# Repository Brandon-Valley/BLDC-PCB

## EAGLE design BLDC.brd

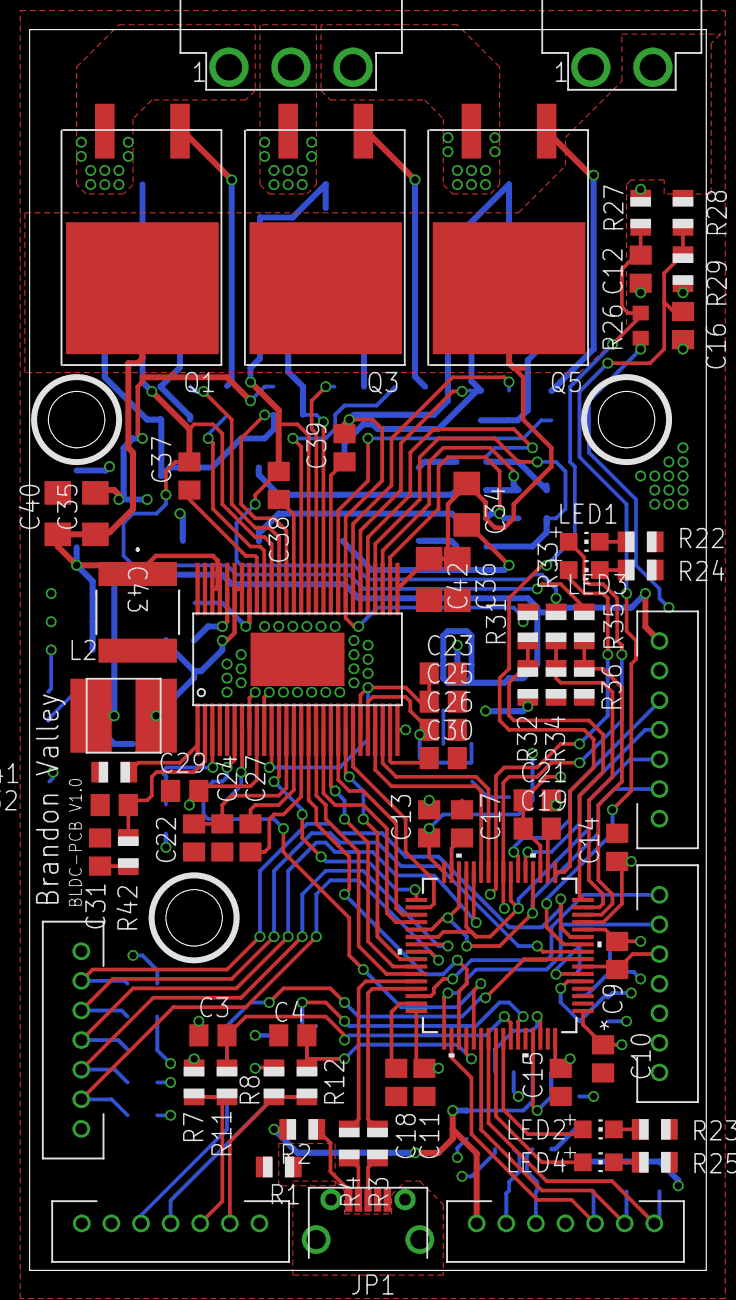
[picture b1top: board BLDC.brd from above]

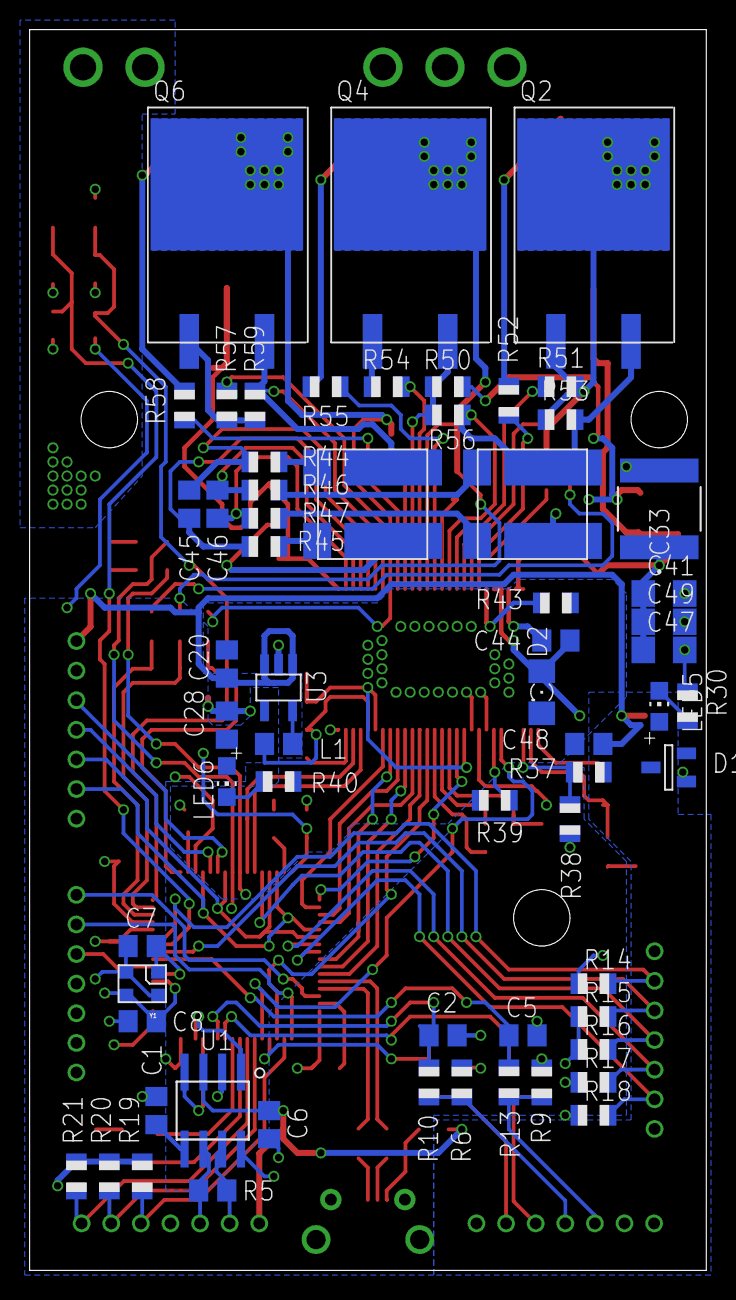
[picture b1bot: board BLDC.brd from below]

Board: 2 copper layers, 45.7 x 83.8 mm, 137 parts (62 on the bottom side), 110 nets.

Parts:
C1, C6: 0.1uF; C0805
C2, C3, C4, C5: 4n7; C0805
C7, C8: 15p; C0805
C9, C16, C44: 100n; C0805
C10, C11, C12, C13, C14, C15, C17, C18, C19, C21, C22, C23, C24, C25, C26, C29, C30: 2.2uf; C0805
C20: 4.7uF; C0805
C27: 22n; C0805
C28: 10uF; C0805
C31: 6.8n; C0805
C32: 120pf; C0805
C33, C43: 15uf,100V; K-55
C34, C35, C36, C40, C41, C42, C47, C49: 10uf,50V; C1206
C37, C38, C39: 220n; C0805
C45, C46: 2.2n; C0805
C48: 100uf; C0805
D1: 5V; SOT-23_DIODE
D2: 1206-DIODE
J1, J2, J3, J4, J5: JST-1X7
J6: IPBT-103-H1-XX-S-RA
J7: IPBT-102-H1-XX-S-RA
JP1: MOLEX-MICROUSB-B-105017-0001
L1: 2.2uH; 0805
L2: 22uH; TYS5040220M-10
LED1, LED2, LED5, LED6: GREEN; CHIP-LED0805
LED3, LED4: RED; CHIP-LED0805
Q1, Q2, Q3, Q4, Q5, Q6: D2PAK
R1, R13, R50: 0k; R0805
R2: DNP; R0805
R3, R4: 22R; R0805
R5: 120R; R0805
R6, R7, R8, R29, R32, R34, R36: 2.2k; R0805
R9, R10, R11, R12, R39: 10k; R0805
R14, R15, R16, R17, R18, R19, R20, R21, R22, R23, R24, R25, R30, R40: 1k; R0805
R26: 10K; 0603
R27: 10K; R0805
R28: 39K; R0805
R31, R33, R35, R53, R56, R59: 39k; R0805
R37: 18K; R0805
R38: 3K3; R0805
R41: 220K; R0805
R42: 15K; R0805
R43: 1M; R0805
R44, R45, R46, R47: 100R; R0805
R48, R49: .001R; 2726
R51, R52, R54, R55, R57, R58: 4.7R; R0805
U1: MCP2562; SOIC8-N_MC
U2: STM32F405RGT6; LQFP-64
U3: LM3671MF-3.3/NOPB; SOT23-5
U4: DRV8302; HTSSOP-56
Y1: 8MHz; 4-SMD

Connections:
+3V3: C1.1, C10.1, C11.1, C13.1, C14.1, C15.1, C19.1, C21.1, C26.1, C28.1, C29.1, J1.P$2, J2.P$6, L1.2, LED6.A, R6.2, R7.2, R8.2, R9.2, R26.2, U1.5, U2.1, U2.13, U2.19, U2.32, U2.48, U2.64, U3.4, U4.9, U4.24
+5V: C6.1, C20.1, C48.1, D1.K, J1.P$1, J3.P$7, J4.P$6, J5.P$7, L2.P$2, LED5.A, R2.2, R37.1, U1.3, U3.1, U3.3
ADC_TEMP: C12.1, R26.1, R27.2, U2.17
AN_IN: C16.1, R28.2, R29.1, U2.10
AUX_1: J5.P$6, R14.2, U2.11
AUX_2: J5.P$5, R15.2, U2.9
AUX_3: J5.P$4, R16.2, U2.28
AUX_4: J5.P$3, R17.2, U2.39
AUX_5: J5.P$2, R18.2, U2.40
AUX_6: J3.P$3, R19.2, U2.50
AUX_7: J3.P$2, R20.2, U2.54
AUX_8: J3.P$1, R21.2, U2.55
BR_SO1: U2.27, U4.25
BR_SO2: U2.26, U4.26
CAR_CAN_N: J3.P$5, R5.1, U1.6
CAR_CAN_P: J3.P$6, R5.2, U1.7
CAR_CAN_RX: U1.4, U2.61
CAR_CAN_TX: U1.1, U2.62
DC_CAL: U2.33, U4.12
EN_GATE: U2.51, U4.16
FAULT: U2.53, U4.6
GND: C1.2, C2.2, C3.2, C4.2, C5.2, C6.2, C7.1, C8.1, C9.2, C10.2, C11.2, C12.2, C13.2, C14.2, C15.2, C16.2, C17.2, C18.2, C19.2, C20.2, C21.2, C22.2, C23.2, C24.2, C25.2, C26.2, C28.2, C29.2, C30.2, C31.2, C32.2, C33.2, C34.2, C35.2, C36.2, C40.2, C41.2, C42.2, C43.2, C47.2, C48.2, C49.2, D1.A, D2.A, J1.P$7, J2.P$7, J3.P$4, J4.P$1, J5.P$1, J7.1, JP1.5, JP1.P$5, R1.1, R14.1, R15.1, R16.1, R17.1, R18.1, R19.1, R20.1, R21.1, R22.1, R23.1, R24.1, R25.1, R27.1, R29.2, R30.1, R32.1, R34.1, R36.1, R38.2, R39.1, R40.1, R41.2, R43.2, R48.BL, R49.BL, R50.1, U1.2, U1.8, U2.12, U2.18, U2.60, U2.63, U3.2, U4.8, U4.10, U4.28, U4.57, Y1.2, Y1.4
H1: U2.43, U4.17
H1_LOW: Q2.A2, R49.BR, R53.2, R56.1, U4.44
H1_VS: C37.2, J6.1, Q1.A2, Q2.K, R35.1, U4.46
H2: U2.42, U4.19
H2_LOW: Q4.A2, R50.2, R56.2, U4.39
H2_VS: C38.2, J6.2, Q3.A2, Q4.K, R33.1, U4.41
H3: U2.41, U4.21
H3_LOW: Q6.A2, R48.BR, R59.2, U4.34
H3_VS: C39.2, J6.3, Q5.A2, Q6.K, R31.1, U4.36
HALL_1_IN: J4.P$4, R6.1, R10.1
HALL_1_OUT: C2.1, R10.2, U2.59
HALL_2_IN: J4.P$3, R7.1, R11.1
HALL_2_OUT: C3.1, R11.2, U2.58
HALL_3_IN: J4.P$2, R8.1, R12.1
HALL_3_OUT: C4.1, R12.2, U2.52
L1: U2.36, U4.18
L2: U2.35, U4.20
L3: U2.34, U4.22
LED_GREEN_1: LED1.A, U2.24
LED_GREEN_2: LED2.A, U2.57
LED_RED_1: LED3.A, U2.25
LED_RED_2: LED4.A, U2.56
MISO_ADC_EXT2: J1.P$3, U2.22
M_H1: R52.1, U4.47
M_H2: R55.1, U4.42
M_H3: R58.1, U4.37
M_L1: R51.1, U4.45
M_L2: R54.1, U4.40
M_L3: R57.1, U4.35
unnamed: LED3.C, R24.2
unnamed: LED2.C, R23.2
unnamed: JP1.2, JP1.P$2, R4.2
unnamed: JP1.3, JP1.P$3, R3.2
unnamed: JP1.1, JP1.P$1, R2.1
unnamed: C18.1, U2.47
unnamed: C8.2, U2.5, Y1.3
unnamed: C7.2, U2.6, Y1.1
unnamed: R41.1, U4.1
unnamed: C31.1, R42.1
unnamed: L1.1, U3.5
unnamed: C32.1, R42.2, U4.2
unnamed: R37.2, R38.1, U4.3
unnamed: R39.2, U4.7
unnamed: C23.1, C25.1, U4.11, U4.23
unnamed: C22.1, C24.1, U4.13
unnamed: C27.1, U4.14
unnamed: C30.1, U4.27
unnamed: C27.2, U4.15
unnamed: C44.1, U4.52
unnamed: C44.2, D2.C, L2.P$1, U4.50, U4.51
unnamed: R43.1, U4.49
unnamed: C37.1, U4.48
unnamed: C45.1, R44.1, U4.33
unnamed: C38.1, U4.43
unnamed: C45.2, R45.1, U4.32
unnamed: C39.1, U4.38
unnamed: C46.2, R47.1, U4.30
unnamed: C46.1, R46.1, U4.31
unnamed: Q1.A1, R52.2
unnamed: Q3.A1, R55.2
unnamed: Q5.A1, R58.2
unnamed: Q2.A1, R51.2, R53.1
unnamed: Q4.A1, R54.2
unnamed: Q6.A1, R57.2, R59.1
unnamed: C17.1, U2.31
unnamed: LED1.C, R22.2
unnamed: LED4.C, R25.2
unnamed: LED5.C, R30.2
unnamed: LED6.C, R40.2
NRST: C9.1, J2.P$3, U2.7
RX_SCL_MOSI: J1.P$5, U2.23, U2.29, U2.38
SCK_ADC_EXT: J1.P$4, U2.21
SENS1: R31.2, R32.2, U2.16
SENS2: R33.2, R34.2, U2.15
SENS3: R35.2, R36.2, U2.14
SGND: JP1.P$6, JP1.P$7, JP1.P$8, JP1.P$9, R1.2
SH1_A: R44.2, R48.TR
SH1_B: R45.2, R48.TL
SH2_A: R46.2, R49.TR
SH2_B: R47.2, R49.TL
SWCLK: J2.P$2, U2.49
SWDIO: J2.P$1, U2.46
TEMP_IN: J4.P$5, R9.1, R13.2
TEMP_MOTOR: C5.1, R13.1, U2.8
TX_SDA_NSS: J1.P$6, U2.20, U2.30, U2.37
USB_DM: R4.1, U2.44
USB_DP: R3.1, U2.45
VCC: C33.1, C34.1, C35.1, C36.1, C40.1, C41.1, C42.1, C43.1, C47.1, C49.1, J7.2, Q1.K, Q3.K, Q5.K, R28.1, U4.29, U4.53, U4.54

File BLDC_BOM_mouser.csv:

Qty-1,Part References,Value,Package,Mfg Part Num,Mfg Name,VID,Vendor Part Num,Description,Pkg Code,,,,,,XREF
1,"J7",,IPBT-102-H1-XX-S-RA,***PART# '*' NOT FOUND***,*,*,*,*,*,*,*,*,*,*,*
1,"J6",,IPBT-103-H1-XX-S-RA,***PART# '*' NOT FOUND***,*,*,*,*,*,*,*,*,*,*,*
5,"J1, J2, J3, J4, J5",,JST-1X7,***PART# '*' NOT FOUND***,*,*,*,*,*,*,*,*,*,*,*
1,"JP1",,MOLEX-MICROUSB-B-105017-0001,***PART# '*' NOT FOUND***,*,*,*,*,*,*,*,*,*,*,*
1,"D2",,1206-DIODE,CD1206-B260,Bourns Inc.,DK,CD1206-B260CT-ND,Diode Schottky 60V 2A Surface Mount 1206,Chip, Concave Terminals,*,*,*,*,*,*
6,"Q1, Q2, Q3, Q4, Q5, Q6",,D2PAK,IRFS7530TRLPBF,Infineon Technologies,DK,IRFS7530TRLPBFCT-ND,N-Channel 60V 195A (Tc) 375W (Tc) Surface Mount D²PAK (TO-263AB),TO-263-7, D²Pak (6 Leads + Tab),*,*,*,*,*,*
2,"R48, R49",.001R,2726,***PART# '*' NOT FOUND***,*,*,*,*,*,*,*,*,*,*,*
2,"C1, C6",0.1uF,C0805,GRM21BR71E104KA01L,Murata Electronics North America,DK,490-1673-1-ND,CAP CER 0.1UF 25V 10% X7R 0805,0805 (2012 Metric),*,*,*,*,*,REF43
3,"R1, R13, R50",0k,R0805,ERJ-6GEY0R00V,Panasonic Electronic Components,DK,P0.0ACT-ND,RES SMD 0.0 OHM JUMPER 1/8W 0805,0805 (2012 Metric),*,*,*,*,*,*
1,"R43",1M,R0805,ERJ-6ENF1004V,Panasonic Electronic Components,DK,P1.00MCCT-ND,RES 1M OHM 1/8W 1% 0805 SMD,0805 (2012 Metric),*,*,*,*,*,REF27
14,"R14, R15, R16, R17, R18, R19, R20, R21, R22, R23, R24, R25, R30, R40",1k,R0805,RMCF0805FT1K00,Stackpole Electronics Inc.,DK,RMCF0805FT1K00CT-ND,RES SMD 1K OHM 1% 1/8W 0805,0805 (2012 Metric),*,*,*,*,*,*
7,"R6, R7, R8, R29, R32, R34, R36",2.2k,R0805,RMCF0805FT2K20,Stackpole Electronics Inc.,DK,RMCF0805FT2K20CT-ND,RES SMD 2.2K OHM 1% 1/8W 0805 ,0805 (2012 Metric),*,*,*,*,*,*
2,"C45, C46",2.2n,C0805,C2012C0G1H222J060AA,TDK Corporation,DK,445-7507-1-ND,CAP CER 2200PF 50V C0G 0805,0805 (2012 Metric),*,*,*,*,*,*
1,"L1",2.2uH,0805,74479775222,Wurth Electronics Inc,DK,732-2953-1-ND,FIXED IND 2.2UH 700MA 230 MOHM,0805 (2012 Metric),*,*,*,*,*,*
17,"C10, C11, C12, C13, C14, C15, C17, C18, C19, C21, C22, C23, C24, C25, C26, C29, C30",2.2uf,C0805,UMK212BB7225KG-T,Taiyo Yuden,DK,587-3169-1-ND,CAP CER 2.2UF 50V X7R 0805,0805 (2012 Metric),*,*,*,*,*,*
1,"R38",3K3,R0805,RMCF0805FT3K30,Stackpole Electronics Inc.,DK,RMCF0805FT3K30CT-ND,RES SMD 3.3K OHM 1% 1/8W 0805,0805 (2012 Metric),*,*,*,*,*,*
6,"R51, R52, R54, R55, R57, R58",4.7R,R0805,ERJ-6RQF4R7V,Panasonic Electronic Components,DK,P4.7DCT-ND,RES SMD 4.7 OHM 1% 1/8W 0805,0805 (2012 Metric),*,*,*,*,*,*
1,"C20",4.7uF,C0805,GRM21BR61E475KA12L,Murata Electronics North America,DK,490-3335-1-ND,CAP CER 4.7UF 25V X5R 0805,0805 (2012 Metric),*,*,*,*,*,*
4,"C2, C3, C4, C5",4n7,C0805,GRM2165C1H472FA01D,Murata Electronics North America,DK,490-8288-1-ND,CAP CER 4700PF 50V C0G/NP0 0805,0805 (2012 Metric),*,*,*,*,*,*
1,"C31",6.8n,C0805,C0805C682K5RACTU,Kemet,DK,399-1157-1-ND,CAP CER 6800PF 50V 10% X7R 0805,0805 (2012 Metric),*,*,*,*,*,*
1,"Y1",8MHz,4-SMD,ABM3B-8.000MHZ-10-1-U-T,Abracon LLC,DK,535-9721-1-ND,8MHz ±10ppm Crystal 10pF 200 Ohm -10°C ~ 60°C  Surface Mount 4-SMD, No Lead,4-SMD, No Lead,*,*,*,*,*,*
1,"R27",10K,R0805,ERJ-6ENF1002V,Panasonic Electronic Components,DK,P10.0KCCT-ND,RES SMD 10K OHM 1% 1/8W 0805,0805 (2012 Metric),*,*,*,*,*,*
1,"R26",10K,0603,NCP18XH103F03RB,Murata Electronics North America,DK,490-4800-1-ND,NTC Thermistor 10k 0603 (1608 Metric),0603 (1608 Metric),*,*,*,*,*,*
5,"R9, R10, R11, R12, R39",10k,R0805,ERJ-6ENF1002V,Panasonic Electronic Components,DK,P10.0KCCT-ND,RES SMD 10K OHM 1% 1/8W 0805,0805 (2012 Metric),*,*,*,*,*,*
1,"C28",10uF,C0805,TMK212BBJ106KG-T,Taiyo Yuden,DK,587-2985-1-ND,CAP CER 10UF 25V X5R 0805,0805 (2012 Metric),*,*,*,*,*,*
8,"C34, C35, C36, C40, C41, C42, C47, C49",10uf,50V,C1206,C3216JB1H106K160AB,TDK Corporation,DK,445-11722-1-ND,CAP CER 10UF 50V 10% JB 1206,1206 (3216 Metric),*,*,*,*,*,REF7
1,"R42",15K,R0805,RMCF0805FT15K0,Stackpole Electronics Inc.,DK,RMCF0805FT15K0CT-ND,RES SMD 15K OHM 1% 1/8W 0805,0805 (2012 Metric),*,*,*,*,*,*
2,"C33, C43",15UF,100V,K-55,KCM55WR72A156MH01K,Murata Electronics North America,DK,490-5838-1-ND, CAP CER 15UF 100V X7R SMD ,Stacked SMD, 2 J-Lead,*,*,*,*,*,*
2,"C7, C8",15p,C0805,CL21C150JBANNNC,Samsung Electro-Mechanics America Inc,DK,1276-1163-1-ND,CAP CER 15PF 50V 5% NP0 0805,0805 (2012 Metric),*,*,*,*,*,*
1,"R37",18K,R0805,ERJ-6ENF1802V,Panasonic Electronic Components,DK,P18.0KCCT-ND,18k Ohm ±1% 0.125W, 1/8W Chip Resistor 0805 (2012 Metric) Automotive AEC-Q200 Thick Film,0805 (2012 Metric),*,*,*,*,*,*
2,"R3, R4",22R,R0805,RMCF0805FT22R0,Stackpole Electronics Inc.,DK,RMCF0805FT22R0CT-ND,RES SMD 22 OHM 1% 1/8W 0805,0805 (2012 Metric),*,*,*,*,*,*
1,"L2",22UH,TYS5040220M-10,TYS5040220M-10,Laird-Signal Integrity Products,DK,240-2713-1-ND,FIXED IND 22UH 1.5A 129 MOHM SMD,Nonstandard,*,*,*,*,*,*
1,"C27",22n,C0805,C2012C0G1H223J125AA,TDK Corporation,DK,445-7522-1-ND,CAP CER 0.022UF 50V 5% C0G 0805,0805 (2012 Metric),*,*,*,*,*,*
1,"R28",39K,R0805,ERJ-6ENF3902V,Panasonic Electronic Components,DK,P39.0KCCT-ND,RES SMD 39K OHM 1% 1/8W 0805,0805 (2012 Metric),*,*,*,*,*,*
6,"R31, R33, R35, R53, R56, R59",39k,R0805,ERJ-6ENF3902V,Panasonic Electronic Components,DK,P39.0KCCT-ND,RES SMD 39K OHM 1% 1/8W 0805,0805 (2012 Metric),*,*,*,*,*,*
4,"R44, R45, R46, R47",100R,R0805,ERJ-6ENF1000V,Panasonic Electronic Components,DK,P100CCT-ND,RES SMD 100 OHM 1% 1/8W 0805,0805 (2012 Metric),*,*,*,*,*,*
3,"C9, C16, C44",100n,C0805,08053C104KAT2A,AVX Corporation,DK,478-3755-1-ND,CAP CER 0.1UF 25V 10% X7R 0805,0805 (2012 Metric),*,*,*,*,*,REF1
1,"C48",100uf,C0805,GRM21BR60G107ME15L,Murata Electronics North America,DK,490-10510-1-ND,CAP CER 100UF 4V X5R 0805,0805 (2012 Metric),*,*,*,*,*,*
1,"R5",120R,R0805,ERJ-6ENF1200V,Panasonic Electronic Components,DK,P120CCT-ND,RES SMD 120 OHM 1% 1/8W 0805,0805 (2012 Metric),*,*,*,*,*,*
1,"C32",120pf,C0805,08051A121FAT2A,AVX Corporation,DK,478-10372-1-ND,CAP CER 120PF 100V NP0 0805,0805 (2012 Metric),*,*,*,*,*,*
1,"R41",220K,R0805,ERJ-6ENF2203V,Panasonic Electronic Components,DK,P220KCCT-ND,220k Ohm ±1% 0.125W, 1/8W Chip Resistor 0805 (2012 Metric) Automotive AEC-Q200 Thick Film,0805 (2012 Metric),*,*,*,*,*,*
3,"C37, C38, C39",220n,C0805,GRM219R71C224KA01D,Murata Electronics North America,DK,490-1684-1-ND,CAP CER 0.22UF 16V X7R 0805,0805 (2012 Metric),*,*,*,*,*,*
1,"D1",568-6471-1-ND,SOT-23_DIODE,SMF5.0A,Littelfuse Inc.,DK,F5748CT-ND,TVS DIODE 5VWM 9.2VC SOD123,SOD-123F,*,*,*,*,*,*
1,"R2",DNP,R0805,ERJ-6GEY0R00V,Panasonic Electronic Components,DK,P0.0ACT-ND,RES SMD 0.0 OHM JUMPER 1/8W 0805,0805 (2012 Metric),*,*,*,*,*,*
1,"U4",DRV8302,HTSSOP-56,DRV8302DCA,Texas Instruments,DK,296-33275-5-ND,Motor Driver Power MOSFET Parallel 56-HTSSOP,56-TFSOP (0.240", 6.10mm Width) Exposed Pad,*,*,*,*,*,*
4,"LED1, LED2, LED5, LED6",GREEN,CHIP-LED0805,598-8170-107F,Dialight,DK,350-2044-1-ND,LED GREEN CLEAR 0805 SMD,0805 (2012 Metric),*,*,*,*,*,*
1,"U3",LM3671MF-3.3/NOPB,SOT23-5,LM3671MF-3.3/NOPB,Texas Instruments,DK,LM3671MF-3.3/NOPBCT-ND,IC REG BUCK 3.3V 0.6A SYNC SOT23,SC-74A, SOT-753,*,*,*,*,*,*
1,"U1",MCP2562,SOIC8-N_MC,MCP2562FD-E/SN,Microchip Technology,DK,MCP2562FD-E/SN-ND,IC TXRX CAN HIGH SPEED VIO 8SOIC,8-SOIC (0.154", 3.90mm Width),*,*,*,*,*,*
2,"LED3, LED4",RED,CHIP-LED0805,5988110107F,Dialight,DK,350-2038-1-ND,LED CHIP RED CLEAR 0805 SMD,0805 (2012 Metric),*,*,*,*,*,*
1,"U2",STM32F405RGT6,LQFP-64,***PART# '*' NOT FOUND***,*,*,*,*,*,*,*,*,*,*,*

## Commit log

2017-01-14 added gitignore
2017-02-07 added minor systems and some stm32 connections
2017-02-15 added DRV8302
2017-02-15 Added gate driver connections
2017-02-16 added power fets
2017-02-17 added debugger
2017-02-17 added CAN connection
2017-02-17 created brd
2017-02-18 Added usb shielding
2017-02-23 added shunts, changed H1_low to GND, and deleted brd
2017-02-24 added DC-DC Converter
2017-02-27 Merge remote-tracking branch 'refs/remotes/origin/master'
    Conflicts:
    BLDC.brd
    BLDC.sch
2017-02-27 Merge remote-tracking branch 'refs/remotes/origin/master' - also added usb shield
    Conflicts:
    BLDC.brd
    BLDC.sch
2017-03-01 added some inputs
2017-03-01 Added note about dc-dc converter
2017-03-01 added dummy aux inputs
2017-03-01 added brd temp and motor temp
2017-03-01 cleaned up sch a bit
2017-03-01 cleaned up sch and added outputs
2017-03-02 added pin headeders and 60V shtky diode
2017-03-02 connected inputs
2017-03-02 Deleted DC-DC Converter
2017-03-03 coinnected dummy aux
2017-03-05 org brd modules
2017-03-05 renumbered parts
2017-03-05 gate driver module progress
2017-03-05 updated BOM
2017-03-07 consdensed gate driver module
2017-03-08 stm32 module progress
2017-03-15 added connector note
2017-03-16 minor stm32 sch change
2017-03-21 2x2 layout org
2017-03-24 added holes
2017-03-24 +3V3 voltage regulator module done
2017-03-27 added aux pulldowns
2017-03-27 Added jst connectors
2017-04-18 added pwr connects
2017-04-18 added stm32 LEDs
2017-04-20 only 8 aux now
2017-04-20 about to change fet driver module
2017-04-20 changed via diameters
2017-04-20 commited to micro JST connectors
2017-06-08 figured out rough layout of connectors
2017-06-09 made very rough boarder dimentions and hole placement
2017-06-10 placed usb connect
2017-06-10 rough layout of all component groups done
2017-06-11 final board dimentions defined
2017-06-30 added jumper so H2_LOW doesn't connect directly to GND b/c Im paranoid
2017-07-01 about to start messing with files
2017-07-02 switched GND and VCC, also a lot of layout progress
2017-07-02 Just made GND plane, about to start fixing bad connections
2017-07-02 layout progress, about to start cleaning up airwires
2017-07-02 airwires cleaned up
2017-07-03 fixed all errors - 1st pass
2017-07-03 added +5V LED
2017-07-03 cleaned brd up a bit
2017-07-03 cleaned up some files
2017-07-03 made sch look all pretty
2017-07-04 moved silks around
2017-07-04 added name and title
2017-07-04 deleted t-place names
2017-07-04 fixed some tiny errors
2017-07-05 added big inductor and updated BOM a bit
2017-07-05 added some large components at the last minute because I am a glutton for punishment
2017-07-06 added jumper for DNP on usb
2017-07-06 fixed brd errors
2017-07-06 made brd look all pretty
2017-07-06 added v1.0 onto brd name
2017-07-06 generated CAMS and cleaned up files
2017-07-13 added mouser bom
2017-07-13 got rid of names
2017-07-13 cleaned up files
2017-07-13 cleaned up 2 ERC errors
2017-07-13 moved silks to the side
2017-09-04 Y1 wrong package

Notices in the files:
parts and their libraries:
COPYRIGHT: Copyright C 2015 Accelerated Designs. All rights reserved
